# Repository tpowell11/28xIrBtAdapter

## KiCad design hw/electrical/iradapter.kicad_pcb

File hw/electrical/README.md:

# Hardware: Electrical
## Fluke's IR-UART
From [this](https://www.eevblog.com/forum/reviews/going-further-with-the-fluke-289/?action=dlattach;attach=16945) document,
we get the commands and the serial port parameters,
but not the specifications of the IR link system.
I had suspected that this was a pair of IR LEDs hooked up to a UART,
but did not have any confirmation.
I asked on the [EEVBlog Forum](https://www.eevblog.com/forum/testgear/fluke-287289-ir-protocol/) and user indeterminate confirmed that the IR link was a UART with IR leds.
The link uses:
| Parameter | Value  |
|-----------|--------|
| Baudrate  | 115200 |
| Data Bits | 8      |
| Stop Bits | 1      |
| Parity    | None   |

## The Implementation
The core of this implementation is the Pi Pico 2 W.
This microcontroller module uses a RP2350 and a Infineon CYW43439 WiFi/Bluetooth chip.

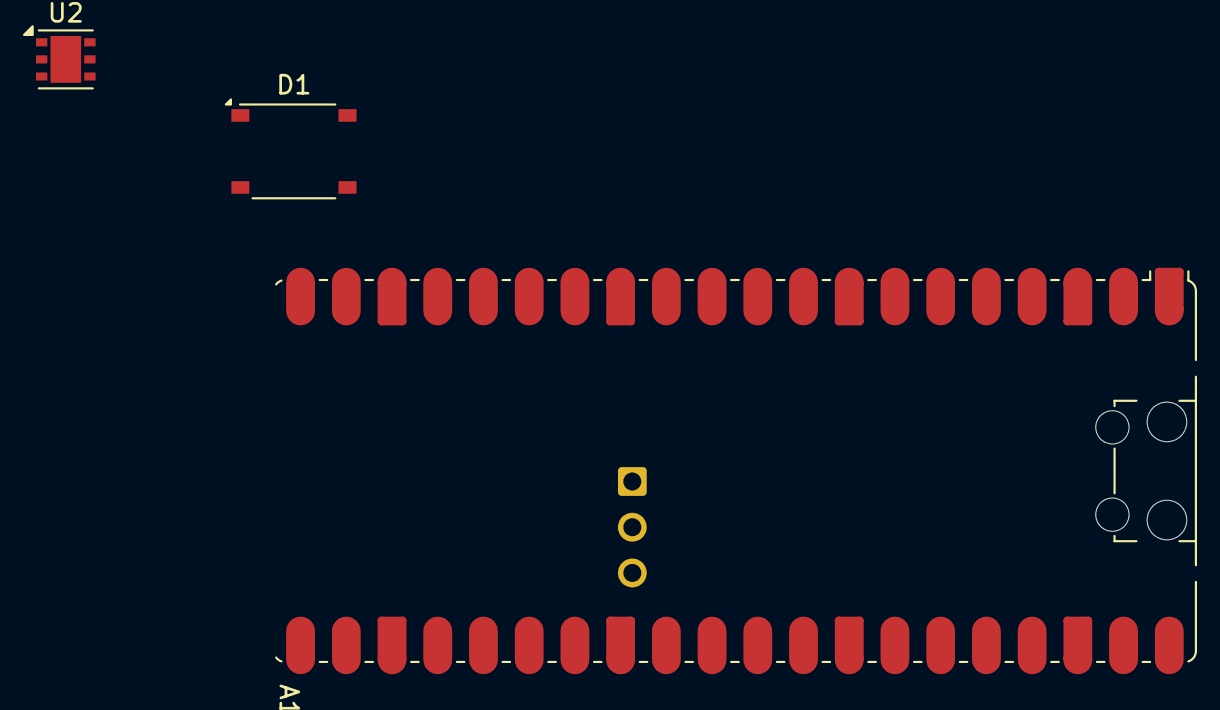
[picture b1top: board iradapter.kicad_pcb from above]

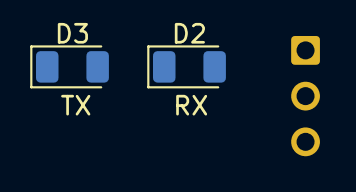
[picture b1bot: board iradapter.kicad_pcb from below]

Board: 2 copper layers, 5 parts (2 on the bottom side), 4 nets, no tracks yet.

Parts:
A1: RaspberryPi_Pico_W; RaspberryPi_Pico_W_SMD_HandSolder
D1: ABS2; Diode_Bridge_Diotec_ABS
D2, D3: IR26-21C_L110_TR8; LED_1206_3216Metric
U2: LDO40LPU33RY; DFN-6-1EP_3x3mm_P0.95mm_EP1.7x2.6mm

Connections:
+3V3: U2.4 (Vout), U2.5 (Vsense)
GND: D1.2 (-), U2.1 (GND), U2.7 (GND)
unnamed: A1.3 (GND), A1.8 (GND), A1.13 (GND), A1.18 (GND), A1.23 (GND), A1.28 (GND), A1.38 (GND)
unnamed: D1.1 (+), U2.2 (EN), U2.3 (Vin)

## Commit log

2025-12-26 update gitignore
2025-12-26 init electronics and code
2025-12-26 readmes and some fw fixes
2025-12-26 add kotlin stuff to gitignore
2025-12-26 kable can be imported into commonMain... only took an hour
2025-12-27 ui prototyping and figuring. where the hell is androidx.navigation?
